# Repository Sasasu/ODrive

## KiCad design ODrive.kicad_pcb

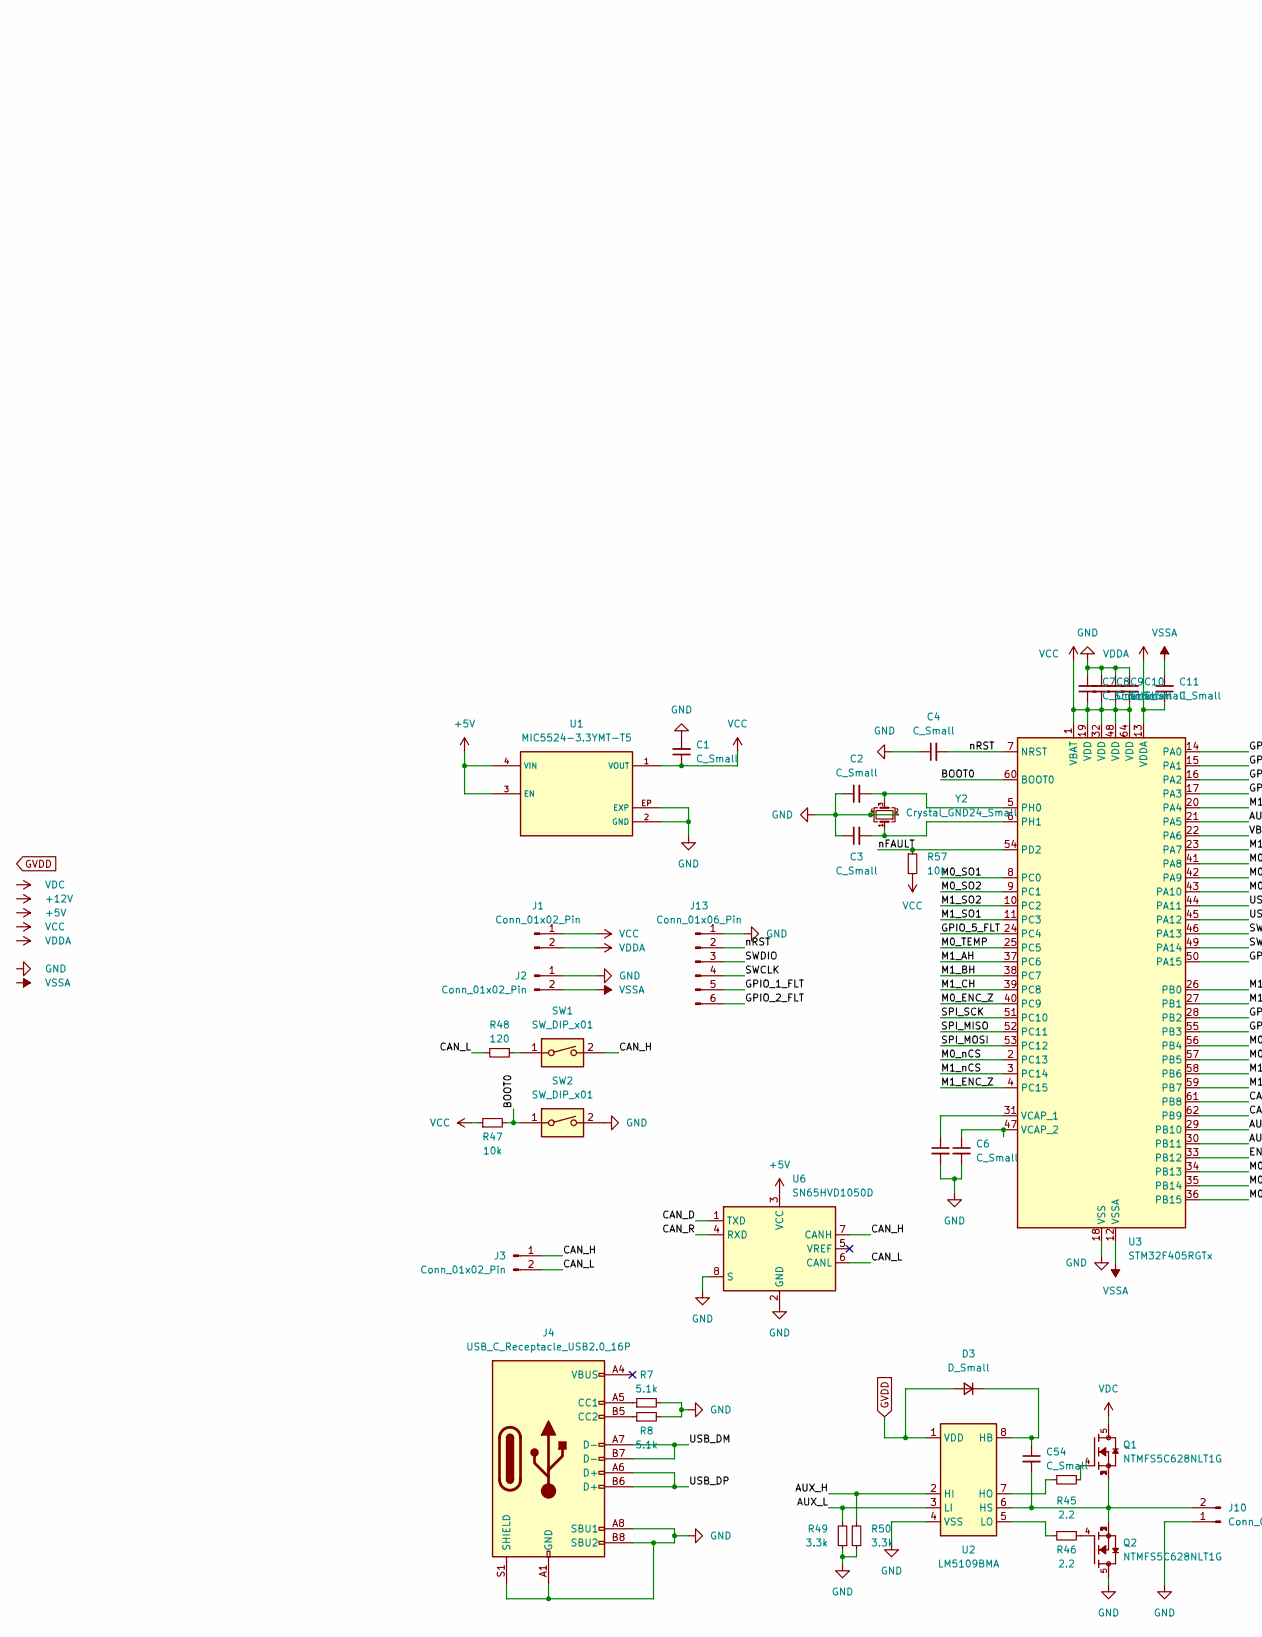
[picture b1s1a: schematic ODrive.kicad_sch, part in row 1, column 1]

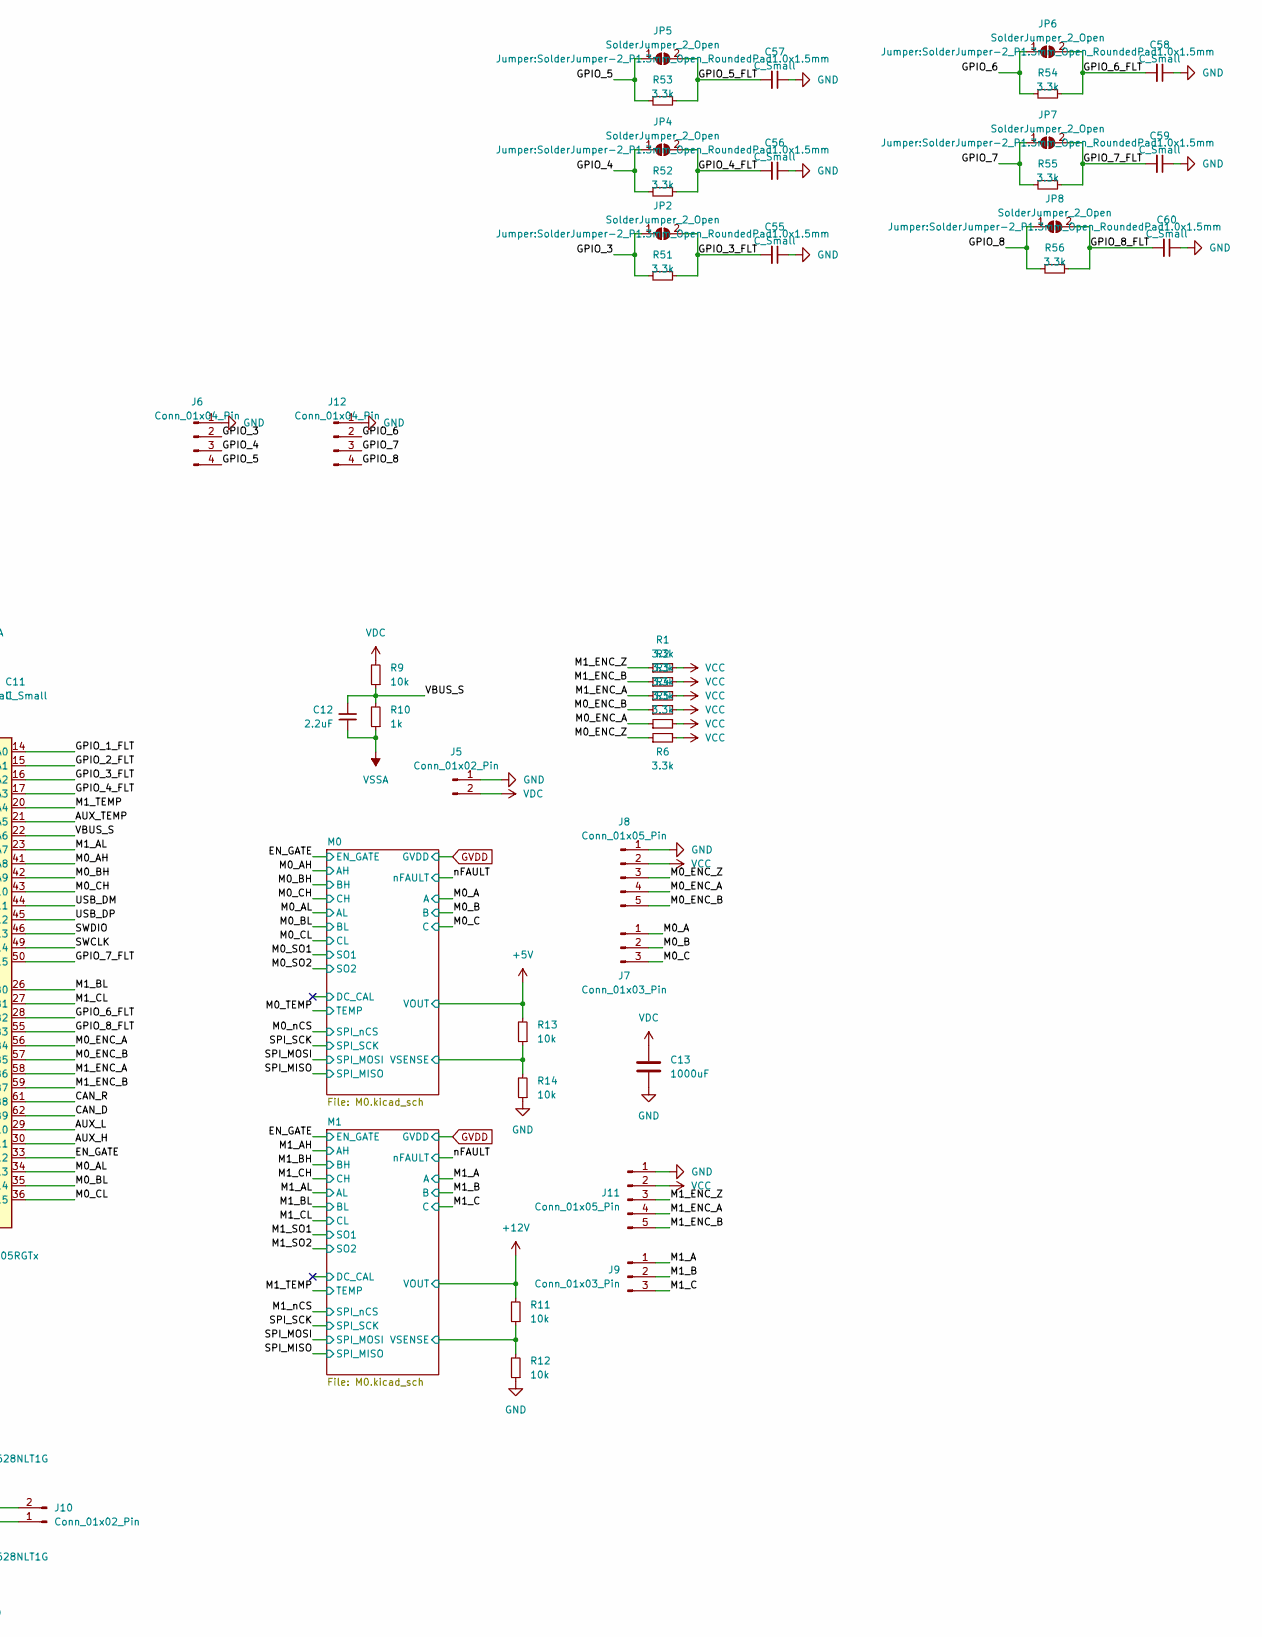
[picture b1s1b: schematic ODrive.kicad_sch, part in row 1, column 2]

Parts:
C1, C2, C3, C4, C5, C6, C7, C8, C9, C10, C11, C54, C55, C56, C57, C58, C59, C60: C_Small; C_0402_1005Metric
C12: 2.2uF; C_0402_1005Metric
C13: 1000uF; C_Radial_D18.0mm_H35.5mm_P7.50mm
D3: D_Small; D_0805_2012Metric
J1, J2, J3: Conn_01x02_Pin; PinHeader_1x02_P2.54mm_Vertical
J4: USB_C_Receptacle_USB2.0_16P; USB_C_Receptacle_Palconn_UTC16-G
J5, J10: Conn_01x02_Pin; XT60PT-M
J6, J12: Conn_01x04_Pin; PinHeader_1x04_P2.54mm_Vertical
J7, J9: Conn_01x03_Pin; MR60-FB
J8, J11: Conn_01x05_Pin; PinHeader_1x05_P2.54mm_Vertical
J13: Conn_01x06_Pin; PinHeader_1x06_P2.54mm_Vertical
JP2, JP4, JP5, JP6, JP7, JP8: SolderJumper_2_Open; SolderJumper-2_P1.3mm_Open_RoundedPad1.0x1.5mm
Q1, Q2: NTMFS5C628NLT1G; TRANS_NTMFS5C628NLT1G; PARTREV 1
R1, R2, R3, R4, R5, R6, R49, R50, R51, R52, R53, R54, R55, R56: 3.3k; R_0402_1005Metric
R7, R8: 5.1k; R_0402_1005Metric
R9, R11, R12, R13, R14, R47, R57: 10k; R_0402_1005Metric
R10: 1k; R_0402_1005Metric
R45, R46: 2.2; R_0402_1005Metric
R48: 120; R_0402_1005Metric
SW1, SW2: SW_DIP_x01; PinHeader_1x02_P2.54mm_Vertical
U1: MIC5524-3.3YMT-T5
U2: LM5109BMA; SOIC-8_3.9x4.9mm_P1.27mm
U3: STM32F405RGTx; LQFP-64_10x10mm_P0.5mm
U6: SN65HVD1050D; SOIC-8_3.9x4.9mm_P1.27mm
Y2: Crystal_GND24_Small; Crystal_SMD_3225-4Pin_3.2x2.5mm

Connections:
+5V: R13.2, U1.3 (EN), U1.4 (VIN), U6.3 (VCC); also elsewhere on the board
+12V: R11.2; also elsewhere on the board
/AUX_H: R50.2, U2.2 (HI), U3.30 (PB11)
/AUX_L: R49.2, U2.3 (LI), U3.29 (PB10)
/AUX_TEMP: U3.21 (PA5)
/BOOT0: R47.2, SW2.1, U3.60 (BOOT0)
/CAN_D: U3.62 (PB9), U6.1 (TXD)
/CAN_H: J3.1, SW1.2, U6.7 (CANH)
/CAN_L: J3.2, R48.2, U6.6 (CANL)
/CAN_R: U3.61 (PB8), U6.4 (RXD)
/EN_GATE: U3.33 (PB12); also elsewhere on the board
/GPIO_1_FLT: J13.5, U3.14 (PA0)
/GPIO_2_FLT: J13.6, U3.15 (PA1)
/GPIO_3: J6.2, JP2.1 (A), R51.2
/GPIO_3_FLT: C55.2, JP2.2 (B), R51.1, U3.16 (PA2)
/GPIO_4: J6.3, JP4.1 (A), R52.2
/GPIO_4_FLT: C56.2, JP4.2 (B), R52.1, U3.17 (PA3)
/GPIO_5: J6.4, JP5.1 (A), R53.2
/GPIO_5_FLT: C57.2, JP5.2 (B), R53.1, U3.24 (PC4)
/GPIO_6: J12.2, JP6.1 (A), R54.2
/GPIO_6_FLT: C58.2, JP6.2 (B), R54.1, U3.28 (PB2)
/GPIO_7: J12.3, JP7.1 (A), R55.2
/GPIO_7_FLT: C59.2, JP7.2 (B), R55.1, U3.50 (PA15)
/GPIO_8: J12.4, JP8.1 (A), R56.2
/GPIO_8_FLT: C60.2, JP8.2 (B), R56.1, U3.55 (PB3)
/M0/VSENSE: R13.1, R14.2; also elsewhere on the board
/M0_A: J7.1; also elsewhere on the board
/M0_AH: U3.41 (PA8); also elsewhere on the board
/M0_AL: U3.34 (PB13); also elsewhere on the board
/M0_B: J7.2; also elsewhere on the board
/M0_BH: U3.42 (PA9); also elsewhere on the board
/M0_BL: U3.35 (PB14); also elsewhere on the board
/M0_C: J7.3; also elsewhere on the board
/M0_CH: U3.43 (PA10); also elsewhere on the board
/M0_CL: U3.36 (PB15); also elsewhere on the board
/M0_ENC_A: J8.4, R5.1, U3.56 (PB4)
/M0_ENC_B: J8.5, R4.1, U3.57 (PB5)
/M0_ENC_Z: J8.3, R6.1, U3.40 (PC9)
/M0_SO1: U3.8 (PC0); also elsewhere on the board
/M0_SO2: U3.9 (PC1); also elsewhere on the board
/M0_TEMP: U3.25 (PC5); also elsewhere on the board
/M0_nCS: U3.2 (PC13); also elsewhere on the board
/M1/VSENSE: R11.1, R12.2; also elsewhere on the board
/M1_A: J9.1; also elsewhere on the board
/M1_AH: U3.37 (PC6); also elsewhere on the board
/M1_AL: U3.23 (PA7); also elsewhere on the board
/M1_B: J9.2; also elsewhere on the board
/M1_BH: U3.38 (PC7); also elsewhere on the board
/M1_BL: U3.26 (PB0); also elsewhere on the board
/M1_C: J9.3; also elsewhere on the board
/M1_CH: U3.39 (PC8); also elsewhere on the board
/M1_CL: U3.27 (PB1); also elsewhere on the board
/M1_ENC_A: J11.4, R3.1, U3.58 (PB6)
/M1_ENC_B: J11.5, R2.1, U3.59 (PB7)
/M1_ENC_Z: J11.3, R1.1, U3.4 (PC15)
/M1_SO1: U3.11 (PC3); also elsewhere on the board
/M1_SO2: U3.10 (PC2); also elsewhere on the board
/M1_TEMP: U3.20 (PA4); also elsewhere on the board
/M1_nCS: U3.3 (PC14); also elsewhere on the board
/SPI_MISO: U3.52 (PC11); also elsewhere on the board
/SPI_MOSI: U3.53 (PC12); also elsewhere on the board
/SPI_SCK: U3.51 (PC10); also elsewhere on the board
/SWCLK: J13.4, U3.49 (PA14)
/SWDIO: J13.3, U3.46 (PA13)
/USB_DM: J4.A7 (D-), J4.B7 (D-), U3.44 (PA11)
/USB_DP: J4.A6 (D+), J4.B6 (D+), U3.45 (PA12)
/VBUS_S: C12.2, R9.1, R10.2, U3.22 (PA6)
/nFAULT: R57.1, U3.54 (PD2); also elsewhere on the board
/nRST: C4.2, J13.2, U3.7 (NRST)
GND: C1.2, C2.1, C3.1, C4.1, C5.2, C6.2, C7.2, C8.2, C9.2, C10.2, C13.2, C55.1, C56.1, C57.1, C58.1, C59.1, C60.1, J2.1, J4.A1 (GND), J4.A8 (SBU1), J4.A12 (GND), J4.B1 (GND), J4.B8 (SBU2), J4.B12 (GND), J4.S1 (SHIELD), J5.1, J6.1, J8.1, J10.1, J11.1, J12.1, J13.1, Q2.5, R7.2, R8.2, R12.1, R14.1, R49.1, R50.1, SW2.2, U1.2 (GND), U1.EP (EXP), U2.4 (VSS), U3.18 (VSS), U3.63 (VSS), U6.2 (GND), U6.8 (S), Y2.2, Y2.4; also elsewhere on the board
GVDD: D3.2 (A), U2.1 (VDD); also elsewhere on the board
unnamed: C54.1, D3.1 (K), U2.8 (HB)
unnamed: J4.A5 (CC1), R7.1
unnamed: J4.B5 (CC2), R8.1
unnamed: C54.2, J10.2, Q1.1, Q1.2, Q1.3, Q2.1, Q2.2, Q2.3, U2.6 (HS)
unnamed: Q1.4, R45.1
unnamed: Q2.4, R46.1
unnamed: R48.1, SW1.1
unnamed: R45.2, U2.7 (HO)
unnamed: R46.2, U2.5 (LO)
unnamed: C2.2, U3.5 (PH0), Y2.3
unnamed: C3.2, U3.6 (PH1), Y2.1
unnamed: C5.1, U3.31 (VCAP_1)
unnamed: C6.1, U3.47 (VCAP_2)
VCC: C1.1, C7.1, C8.1, C9.1, C10.1, J1.1, J8.2, J11.2, R1.2, R2.2, R3.2, R4.2, R5.2, R6.2, R47.1, R57.2, U1.1 (VOUT), U3.1 (VBAT), U3.19 (VDD), U3.32 (VDD), U3.48 (VDD), U3.64 (VDD); also elsewhere on the board
VDC: C13.1, J5.2, Q1.5, R9.2; also elsewhere on the board
VDDA: C11.1, J1.2, U3.13 (VDDA); also elsewhere on the board
VSSA: C11.2, C12.1, J2.2, R10.1, U3.12 (VSSA); also elsewhere on the board

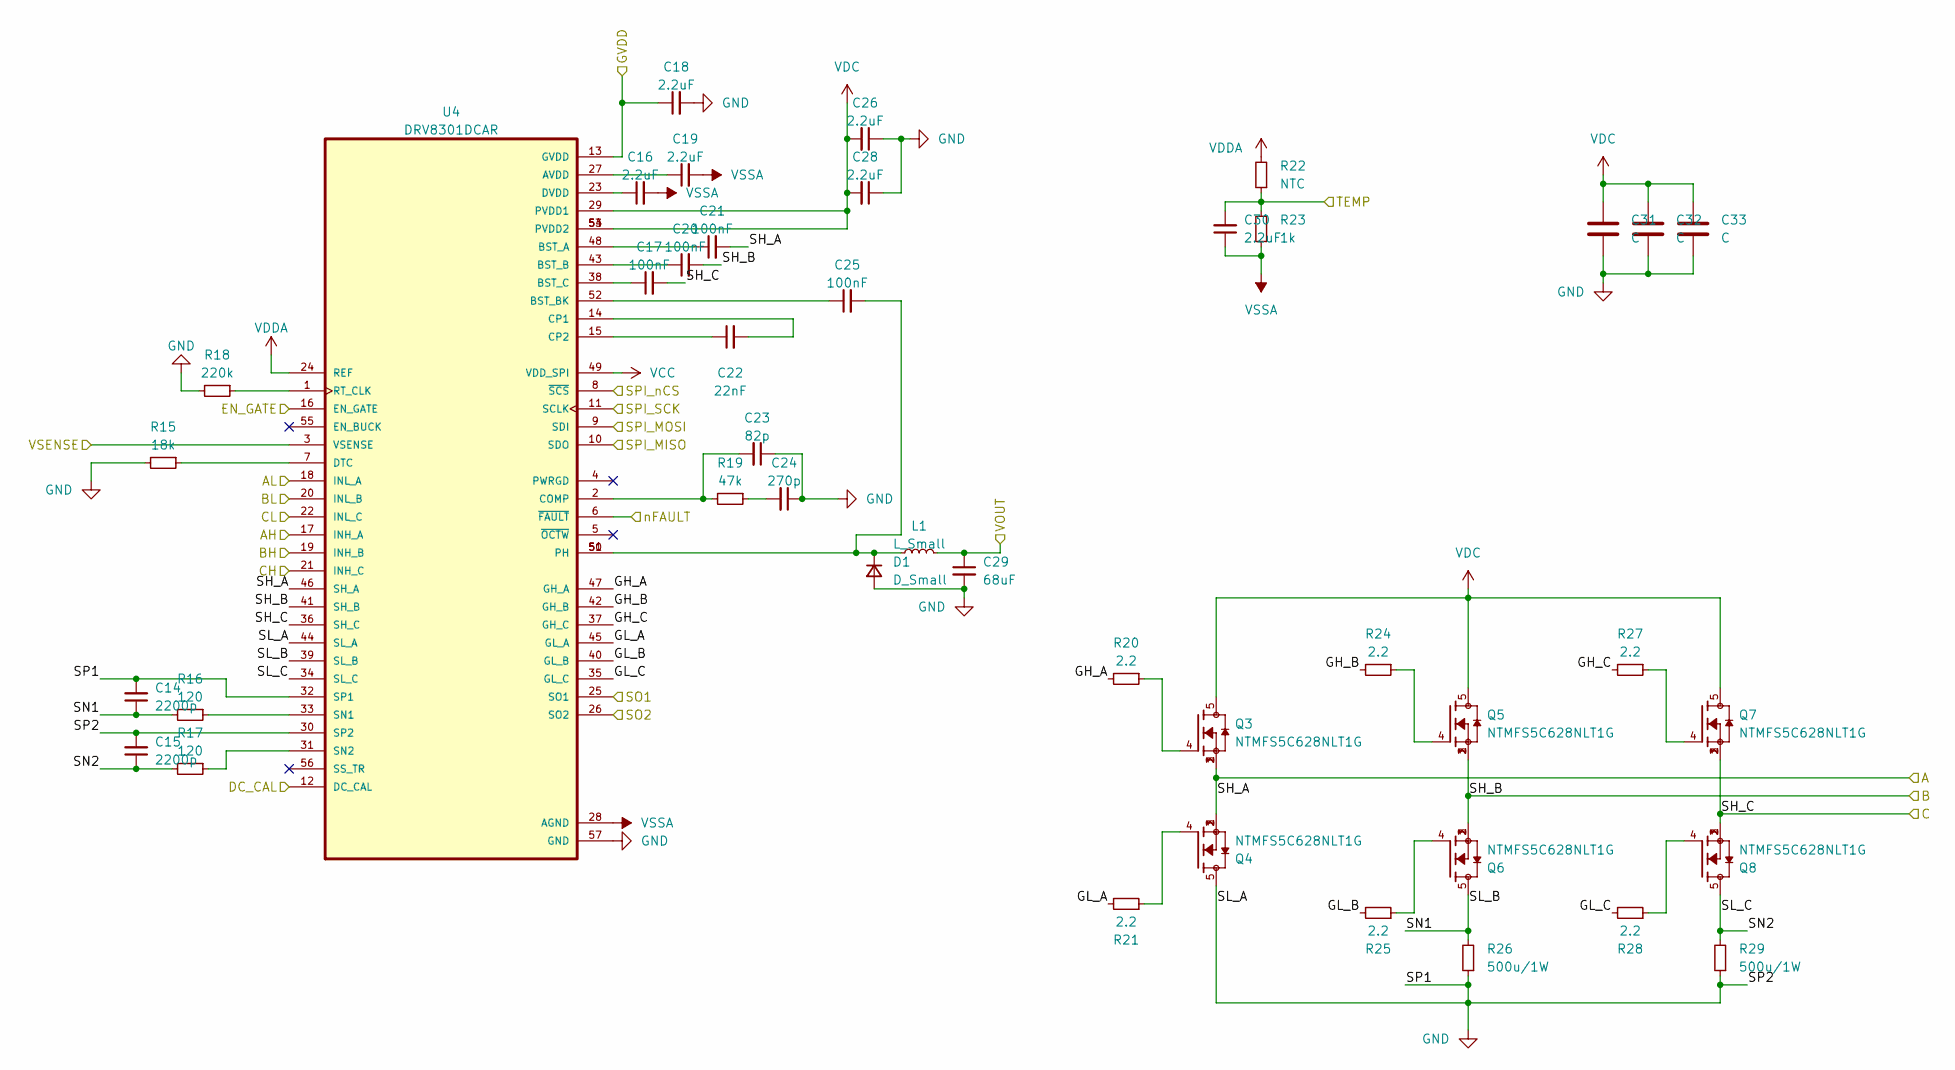
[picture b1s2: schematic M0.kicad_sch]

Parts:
C14, C15: 2200p; C_0402_1005Metric
C16, C18, C19, C26, C28, C30: 2.2uF; C_0402_1005Metric
C17, C20, C21, C25: 100nF; C_0402_1005Metric
C22: 22nF; C_0402_1005Metric
C23: 82p; C_0402_1005Metric
C24: 270p; C_0402_1005Metric
C29: 68uF; C_0603_1608Metric
C31, C32, C33: C; C_1206_3216Metric
D1: D_Small; D_0805_2012Metric
L1: L_Small; L_1210_3225Metric
Q3, Q4, Q5, Q6, Q7, Q8: NTMFS5C628NLT1G; TRANS_NTMFS5C628NLT1G; PARTREV 1
R15: 18k; R_0402_1005Metric
R16, R17: 120; R_0402_1005Metric
R18: 220k; R_0402_1005Metric
R19: 47k; R_0402_1005Metric
R20, R21, R24, R25, R27, R28: 2.2; R_0402_1005Metric
R22: NTC; R_0402_1005Metric
R23: 1k; R_0402_1005Metric
R26, R29: 500u/1W; R_1206_3216Metric
U4: DRV8301DCAR; SOP50P810X120-57N; PARTREV F

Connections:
+5V: C29.1, L1.2; also elsewhere on the board
/EN_GATE: U4.16 (EN_GATE); also elsewhere on the board
/M0/DC_CAL: U4.12 (DC_CAL)
/M0/GH_A: R20.2, U4.47 (GH_A)
/M0/GH_B: R24.2, U4.42 (GH_B)
/M0/GH_C: R27.2, U4.37 (GH_C)
/M0/GL_A: R21.2, U4.45 (GL_A)
/M0/GL_B: R25.2, U4.40 (GL_B)
/M0/GL_C: R28.2, U4.35 (GL_C)
/M0/SL_B: C14.1, Q6.5, R16.2, R26.2, U4.39 (SL_B)
/M0/SL_C: C15.1, Q8.5, R17.2, R29.2, U4.34 (SL_C)
/M0/VSENSE: U4.3 (VSENSE); also elsewhere on the board
/M0_A: C21.2, Q3.1, Q3.2, Q3.3, Q4.1, Q4.2, Q4.3, U4.46 (SH_A); also elsewhere on the board
/M0_AH: U4.17 (INH_A); also elsewhere on the board
/M0_AL: U4.18 (INL_A); also elsewhere on the board
/M0_B: C20.2, Q5.1, Q5.2, Q5.3, Q6.1, Q6.2, Q6.3, U4.41 (SH_B); also elsewhere on the board
/M0_BH: U4.19 (INH_B); also elsewhere on the board
/M0_BL: U4.20 (INL_B); also elsewhere on the board
/M0_C: C17.2, Q7.1, Q7.2, Q7.3, Q8.1, Q8.2, Q8.3, U4.36 (SH_C); also elsewhere on the board
/M0_CH: U4.21 (INH_C); also elsewhere on the board
/M0_CL: U4.22 (INL_C); also elsewhere on the board
/M0_SO1: U4.25 (SO1); also elsewhere on the board
/M0_SO2: U4.26 (SO2); also elsewhere on the board
/M0_TEMP: C30.2, R22.1, R23.2; also elsewhere on the board
/M0_nCS: U4.8 (~SCS); also elsewhere on the board
/SPI_MISO: U4.10 (SDO); also elsewhere on the board
/SPI_MOSI: U4.9 (SDI); also elsewhere on the board
/SPI_SCK: U4.11 (SCLK); also elsewhere on the board
/nFAULT: U4.6 (~FAULT); also elsewhere on the board
GND: C14.2, C15.2, C18.2, C23.1, C24.1, C26.1, C28.1, C29.2, C31.2, C32.2, C33.2, D1.2 (A), Q4.5, R15.2, R18.2, R26.1, R29.1, U4.30 (SP2), U4.32 (SP1), U4.44 (SL_A), U4.57 (GND); also elsewhere on the board
GVDD: C18.1, U4.13 (GVDD); also elsewhere on the board
unnamed: C24.2, R19.1
unnamed: C25.2, D1.1 (K), L1.1, U4.50 (PH), U4.51 (PH)
unnamed: Q3.4, R20.1
unnamed: Q4.4, R21.1
unnamed: Q5.4, R24.1
unnamed: Q6.4, R25.1
unnamed: Q7.4, R27.1
unnamed: Q8.4, R28.1
unnamed: C19.1, U4.27 (AVDD)
unnamed: C21.1, U4.48 (BST_A)
unnamed: C20.1, U4.43 (BST_B)
unnamed: C25.1, U4.52 (BST_BK)
unnamed: C17.1, U4.38 (BST_C)
unnamed: C23.2, R19.2, U4.2 (COMP)
unnamed: C22.2, U4.14 (CP1)
unnamed: C22.1, U4.15 (CP2)
unnamed: R15.1, U4.7 (DTC)
unnamed: C16.1, U4.23 (DVDD)
unnamed: R18.1, U4.1 (RT_CLK)
unnamed: R16.1, U4.33 (SN1)
unnamed: R17.1, U4.31 (SN2)
VCC: U4.49 (VDD_SPI); also elsewhere on the board
VDC: C26.2, C28.2, C31.1, C32.1, C33.1, Q3.5, Q5.5, Q7.5, U4.29 (PVDD1), U4.53 (PVDD2), U4.54 (PVDD2); also elsewhere on the board
VDDA: R22.2, U4.24 (REF); also elsewhere on the board
VSSA: C16.2, C19.2, C30.1, R23.1, U4.28 (AGND); also elsewhere on the board

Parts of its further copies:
C34, C35: 2200p; C_0402_1005Metric
C36, C38, C39, C46, C48, C50: 2.2uF; C_0402_1005Metric
C37, C40, C41, C45: 100nF; C_0402_1005Metric
C42: 22nF; C_0402_1005Metric
C43: 82p; C_0402_1005Metric
C44: 270p; C_0402_1005Metric
C49: 68uF; C_0603_1608Metric
C51, C52, C53: C; C_1206_3216Metric
D2: D_Small; D_0805_2012Metric
L2: L_Small; L_1210_3225Metric
Q9, Q10, Q11, Q12, Q13, Q14: NTMFS5C628NLT1G; TRANS_NTMFS5C628NLT1G; PARTREV 1
R30: 18k; R_0402_1005Metric
R31, R32: 120; R_0402_1005Metric
R33: 220k; R_0402_1005Metric
R34: 47k; R_0402_1005Metric
R35, R36, R39, R40, R42, R43: 2.2; R_0402_1005Metric
R37: NTC; R_0402_1005Metric
R38: 1k; R_0402_1005Metric
R41, R44: 500u/1W; R_1206_3216Metric
U5: DRV8301DCAR; SOP50P810X120-57N; PARTREV F

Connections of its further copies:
+12V: C49.1, L2.2; also elsewhere on the board
/EN_GATE: U5.16 (EN_GATE); also elsewhere on the board
/M1/DC_CAL: U5.12 (DC_CAL)
/M1/GH_A: R35.2, U5.47 (GH_A)
/M1/GH_B: R39.2, U5.42 (GH_B)
/M1/GH_C: R42.2, U5.37 (GH_C)
/M1/GL_A: R36.2, U5.45 (GL_A)
/M1/GL_B: R40.2, U5.40 (GL_B)
/M1/GL_C: R43.2, U5.35 (GL_C)
/M1/SL_B: C34.1, Q12.5, R31.2, R41.2, U5.39 (SL_B)
/M1/SL_C: C35.1, Q14.5, R32.2, R44.2, U5.34 (SL_C)
/M1/VSENSE: U5.3 (VSENSE); also elsewhere on the board
/M1_A: C41.2, Q9.1, Q9.2, Q9.3, Q10.1, Q10.2, Q10.3, U5.46 (SH_A); also elsewhere on the board
/M1_AH: U5.17 (INH_A); also elsewhere on the board
/M1_AL: U5.18 (INL_A); also elsewhere on the board
/M1_B: C40.2, Q11.1, Q11.2, Q11.3, Q12.1, Q12.2, Q12.3, U5.41 (SH_B); also elsewhere on the board
/M1_BH: U5.19 (INH_B); also elsewhere on the board
/M1_BL: U5.20 (INL_B); also elsewhere on the board
/M1_C: C37.2, Q13.1, Q13.2, Q13.3, Q14.1, Q14.2, Q14.3, U5.36 (SH_C); also elsewhere on the board
/M1_CH: U5.21 (INH_C); also elsewhere on the board
/M1_CL: U5.22 (INL_C); also elsewhere on the board
/M1_SO1: U5.25 (SO1); also elsewhere on the board
/M1_SO2: U5.26 (SO2); also elsewhere on the board
/M1_TEMP: C50.2, R37.1, R38.2; also elsewhere on the board
/M1_nCS: U5.8 (~SCS); also elsewhere on the board
/SPI_MISO: U5.10 (SDO); also elsewhere on the board
/SPI_MOSI: U5.9 (SDI); also elsewhere on the board
/SPI_SCK: U5.11 (SCLK); also elsewhere on the board
/nFAULT: U5.6 (~FAULT); also elsewhere on the board
GND: C34.2, C35.2, C38.2, C43.1, C44.1, C46.1, C48.1, C49.2, C51.2, C52.2, C53.2, D2.2 (A), Q10.5, R30.2, R33.2, R41.1, R44.1, U5.30 (SP2), U5.32 (SP1), U5.44 (SL_A), U5.57 (GND); also elsewhere on the board
GVDD: C38.1, U5.13 (GVDD); also elsewhere on the board
unnamed: C44.2, R34.1
unnamed: C45.2, D2.1 (K), L2.1, U5.50 (PH), U5.51 (PH)
unnamed: Q9.4, R35.1
unnamed: Q10.4, R36.1
unnamed: Q11.4, R39.1
unnamed: Q12.4, R40.1
unnamed: Q13.4, R42.1
unnamed: Q14.4, R43.1
unnamed: C39.1, U5.27 (AVDD)
unnamed: C41.1, U5.48 (BST_A)
unnamed: C40.1, U5.43 (BST_B)
unnamed: C45.1, U5.52 (BST_BK)
unnamed: C37.1, U5.38 (BST_C)
unnamed: C43.2, R34.2, U5.2 (COMP)
unnamed: C42.2, U5.14 (CP1)
unnamed: C42.1, U5.15 (CP2)
unnamed: R30.1, U5.7 (DTC)
unnamed: C36.1, U5.23 (DVDD)
unnamed: R33.1, U5.1 (RT_CLK)
unnamed: R31.1, U5.33 (SN1)
unnamed: R32.1, U5.31 (SN2)
VCC: U5.49 (VDD_SPI); also elsewhere on the board
VDC: C46.2, C48.2, C51.1, C52.1, C53.1, Q9.5, Q11.5, Q13.5, U5.29 (PVDD1), U5.53 (PVDD2), U5.54 (PVDD2); also elsewhere on the board
VDDA: R37.2, U5.24 (REF); also elsewhere on the board
VSSA: C36.2, C39.2, C50.1, R38.1, U5.28 (AGND); also elsewhere on the board

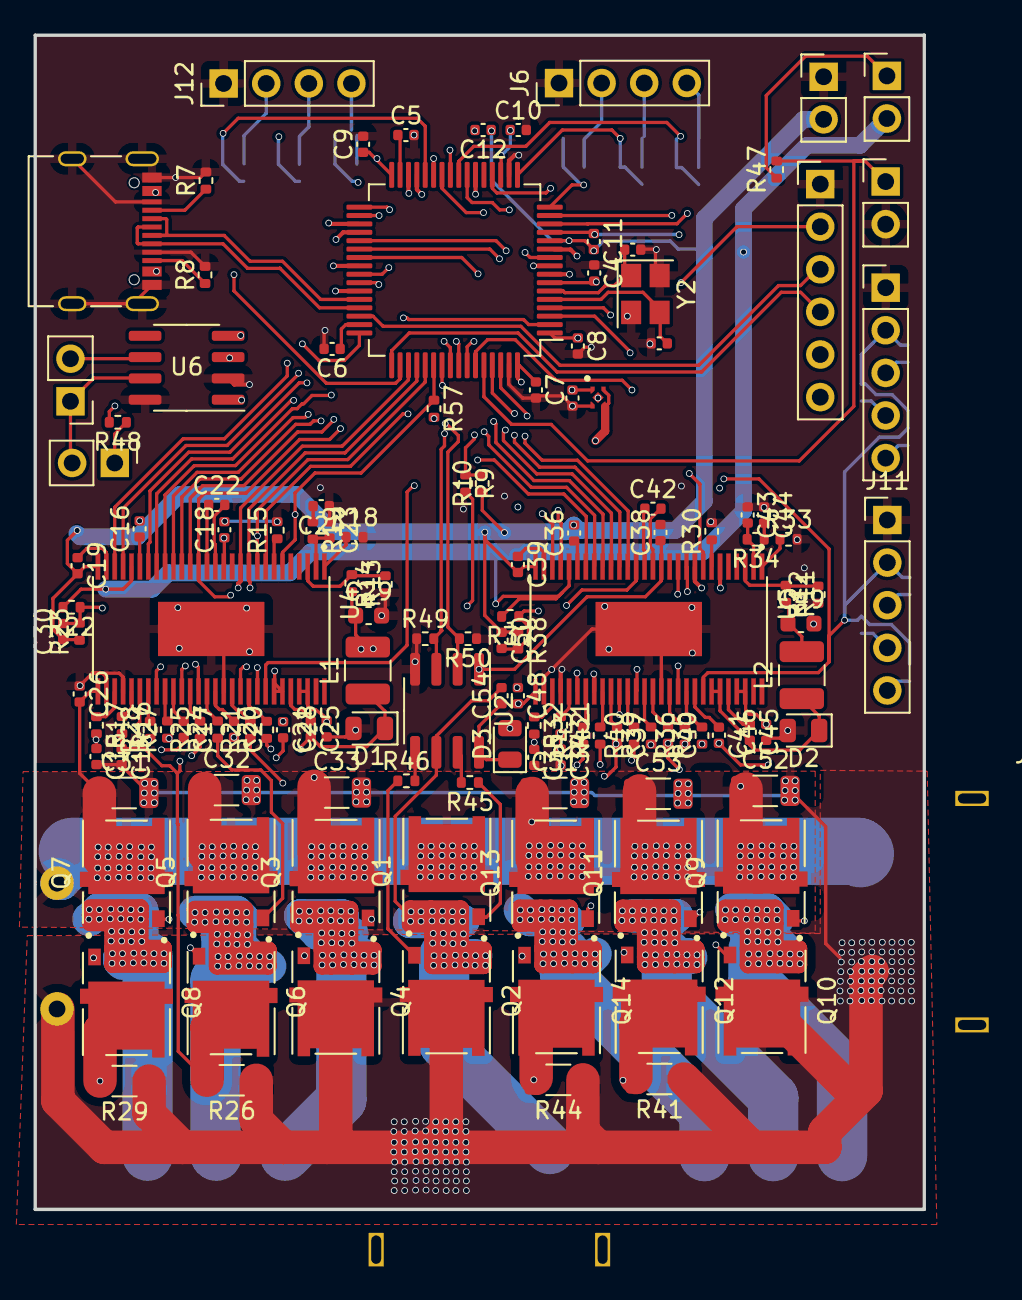
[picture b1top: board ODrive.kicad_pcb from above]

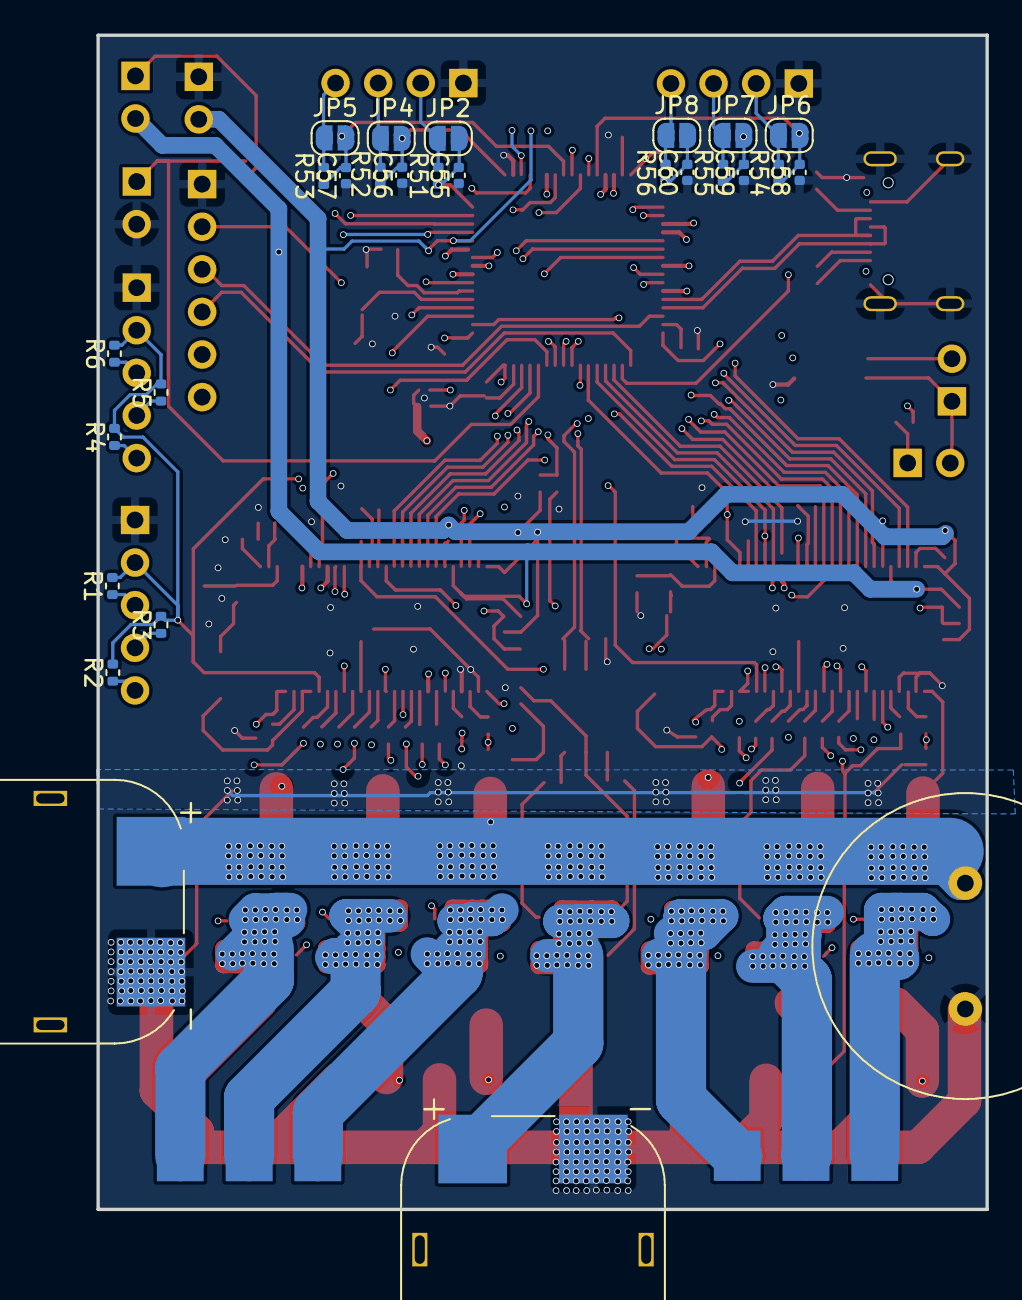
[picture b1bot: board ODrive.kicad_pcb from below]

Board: 4 copper layers, 53.0 x 70.0 mm, 162 parts (29 on the bottom side), 145 nets.

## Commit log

2024-02-16 init
2024-02-19 0.4/0.3
